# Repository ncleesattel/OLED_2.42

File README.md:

## OLED 242 pcb
This is an alternative pcb to the one provided by DIYmore.
A key difference is that no smd soldering is necessary to switch from SPI mode to I2C mode.
Instead there is a switch pad that can be used.

I use this pcb to connect 2.42 inch displays from Aliexpress to either my SHC build or the ESP32 dew heater.
Look for 2.42" 128x64 SSD1309 displays and the assoc. metal frame.

## ordering
The pcb is designed in KiCad.  
In the jlcpcb folder you can find the Gerber, BOM and CPL file you need to not only order the pcb, but also the assembled smd parts.

## cost estimate
| Item | Number | Cost |
|------|--------|------|
| pcb | 5 | 60 |
| frame | 5 | 13 |
| display | 5 | 52 |

Best case you can use all displays equals to 25/unit.  
Worst case you just need one and can't share the cost of the other four equals to 125. 

## pictures

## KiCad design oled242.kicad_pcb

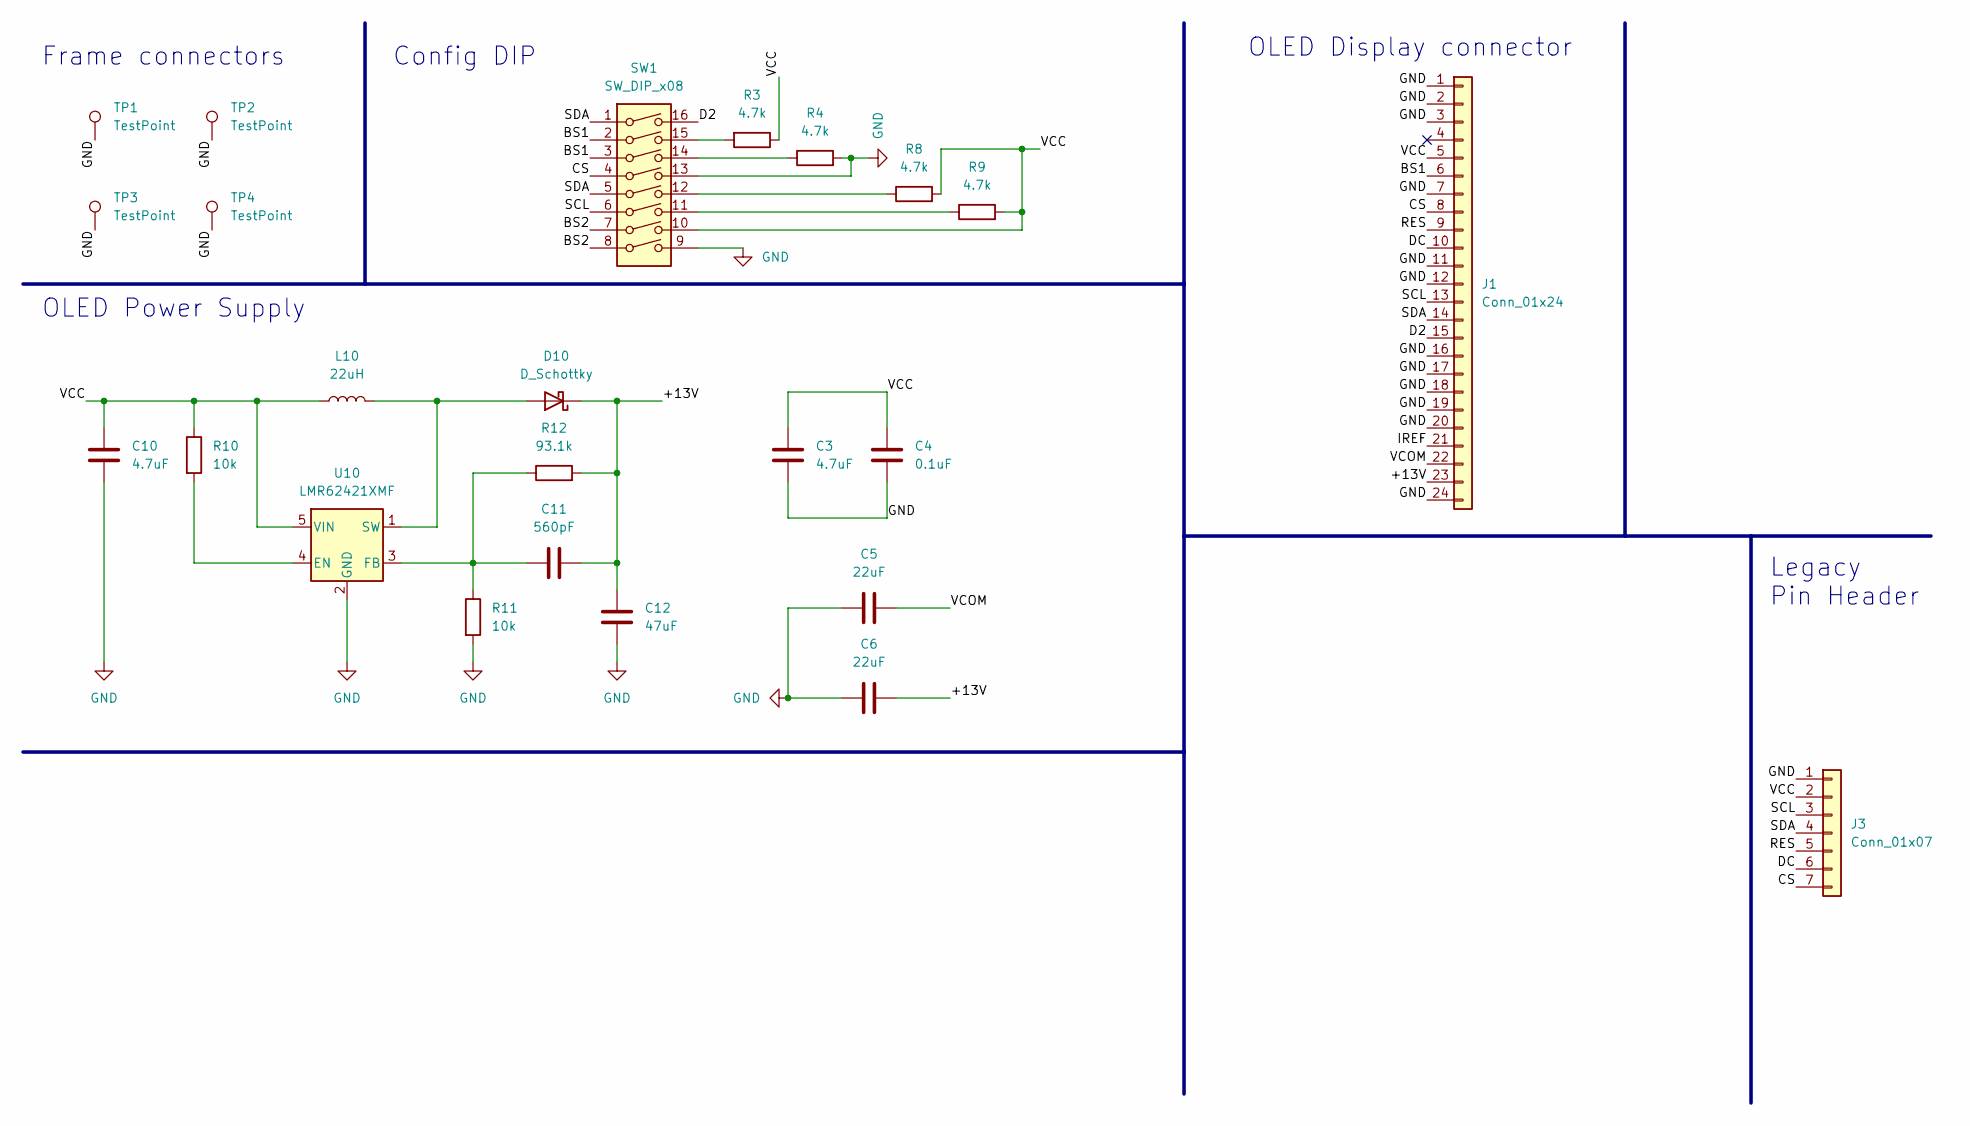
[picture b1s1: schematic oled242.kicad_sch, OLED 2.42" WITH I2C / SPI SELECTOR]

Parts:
C3: 4.7uF; C_0805_2012Metric; LCSC C1779
C4: 0.1uF; C_0603_1608Metric; LCSC C14663
C5, C6: 22uF; C_1206_3216Metric; LCSC C12891
C10: 4.7uF; C_0402_1005Metric; LCSC C23733
C11: 560pF; C_0402_1005Metric; LCSC C464953
C12: 47uF; C_1210_3225Metric; LCSC C77101
D10: D_Schottky; D_SOD-323; LCSC C191023
J1: Conn_01x24; Hirose_FH12-24S-0.5SH_1x24-1MP_P0.50mm_Horizontal; LCSC C506794
J3: Conn_01x07; PinHeader_1x07_P2.54mm_Vertical
L10: 22uH; C_1210_3225Metric; LCSC C223225
R3, R4, R8, R9: 4.7k; R_0603_1608Metric; LCSC C23162
R10, R11: 10k; R_0603_1608Metric; LCSC C25804
R12: 93.1k; R_0603_1608Metric; LCSC C705799
SW1: SW_DIP_x08; SW_DIP_SPSTx08_Slide_Omron_A6H-8101_W6.15mm_P1.27mm; LCSC C224998
TP1, TP2, TP3, TP4: TestPoint; OLED_slot
U10: LMR62421XMF; SOT-23-5; LCSC C206031

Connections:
/+13V: C6.2, C11.2, C12.2, D10.1 (K), J1.23, R12.2
/BS1: J1.6, SW1.2, SW1.3
/BS2: SW1.7, SW1.8
/CS: J1.8, J3.7, SW1.4
/D2: J1.15, SW1.16
/DC: J1.10, J3.6
/IREF: J1.21
/RES: J1.9, J3.5
/SCL: J1.13, J3.3, SW1.6
/SDA: J1.14, J3.4, SW1.1, SW1.5
/VCC: C3.1, C4.1, C10.1, J1.5, J3.2, L10.1, R3.1, R8.2, R9.2, R10.1, SW1.10, U10.5 (VIN)
/VCOM: C5.2, J1.22
GND: C3.2, C4.2, C5.1, C6.1, C10.2, C12.1, J1.1, J1.2, J1.3, J1.7, J1.11, J1.12, J1.16, J1.17, J1.18, J1.19, J1.20, J1.24, J3.1, R4.2, R11.2, SW1.9, SW1.13, TP1.1, TP2.1, TP3.1, TP4.1, U10.2 (GND)
unnamed: D10.2 (A), L10.2, U10.1 (SW)
unnamed: R3.2, SW1.15
unnamed: R4.1, SW1.14
unnamed: R8.1, SW1.12
unnamed: R9.1, SW1.11
unnamed: R10.2, U10.4 (EN)
unnamed: C11.1, R11.1, R12.1, U10.3 (FB)

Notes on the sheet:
Frame connectors
Legacy Pin Header
OLED Display connector
OLED Power Supply
Config DIP

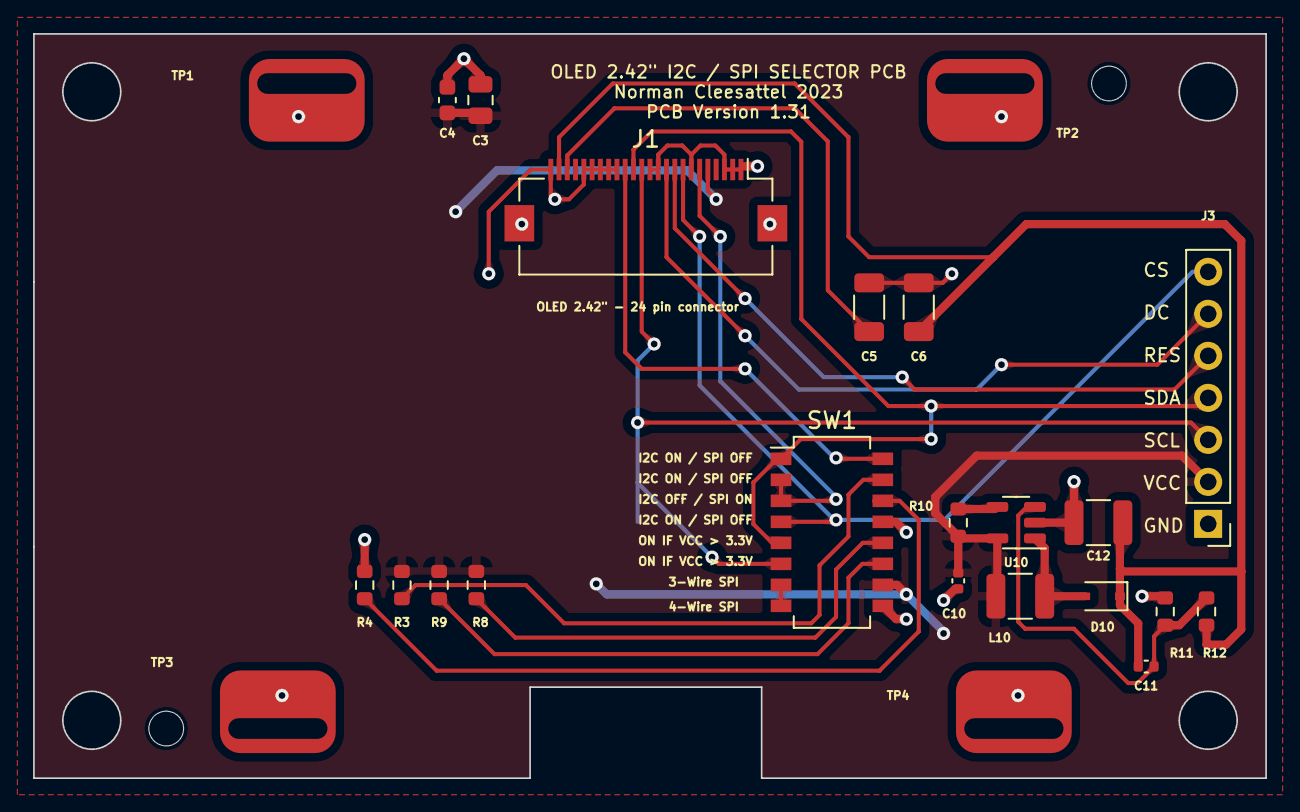
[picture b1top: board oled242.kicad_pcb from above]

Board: 2 copper layers, 74.5 x 45.0 mm, 24 parts (0 on the bottom side), 19 nets.

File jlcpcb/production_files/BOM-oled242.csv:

Comment,Designator,Footprint,LCSC
22uF,"C5,C6",C_1206_3216Metric,C12891
0.1uF,C4,C_0603_1608Metric,C14663
4.7uF,C3,C_0805_2012Metric,C1779
D_Schottky,D10,D_SOD-323,C191023
Conn_01x24,J1,Hirose_FH12-24S-0.5SH_1x24-1MP_P0.50mm_Horizontal,C202112
LMR62421XMF,U10,SOT-23-5,C206031
22uH,L10,C_1210_3225Metric,C223225
SW_DIP_x08,SW1,SW_DIP_SPSTx08_Slide_Omron_A6H-8101_W6.15mm_P1.27mm,C224998
4.7k,"R3,R4,R8,R9",R_0603_1608Metric,C23162
4.7uF,C10,C_0402_1005Metric,C23733
10k,"R10,R11",R_0603_1608Metric,C25804
560pF,C11,C_0402_1005Metric,C464953
93.1k,R12,R_0603_1608Metric,C705799
47uF,C12,C_1210_3225Metric,C77101
TestPoint,TP2,OLED_slot,
OLED_slot,TP4,OLED_slot,
Conn_01x07,J3,PinHeader_1x07_P2.54mm_Vertical,
TestPoint,TP3,OLED_slot,
TestPoint,TP1,OLED_slot,

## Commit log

2023-09-25 Initial upload
2023-09-25 Update README.md
    update path to img
